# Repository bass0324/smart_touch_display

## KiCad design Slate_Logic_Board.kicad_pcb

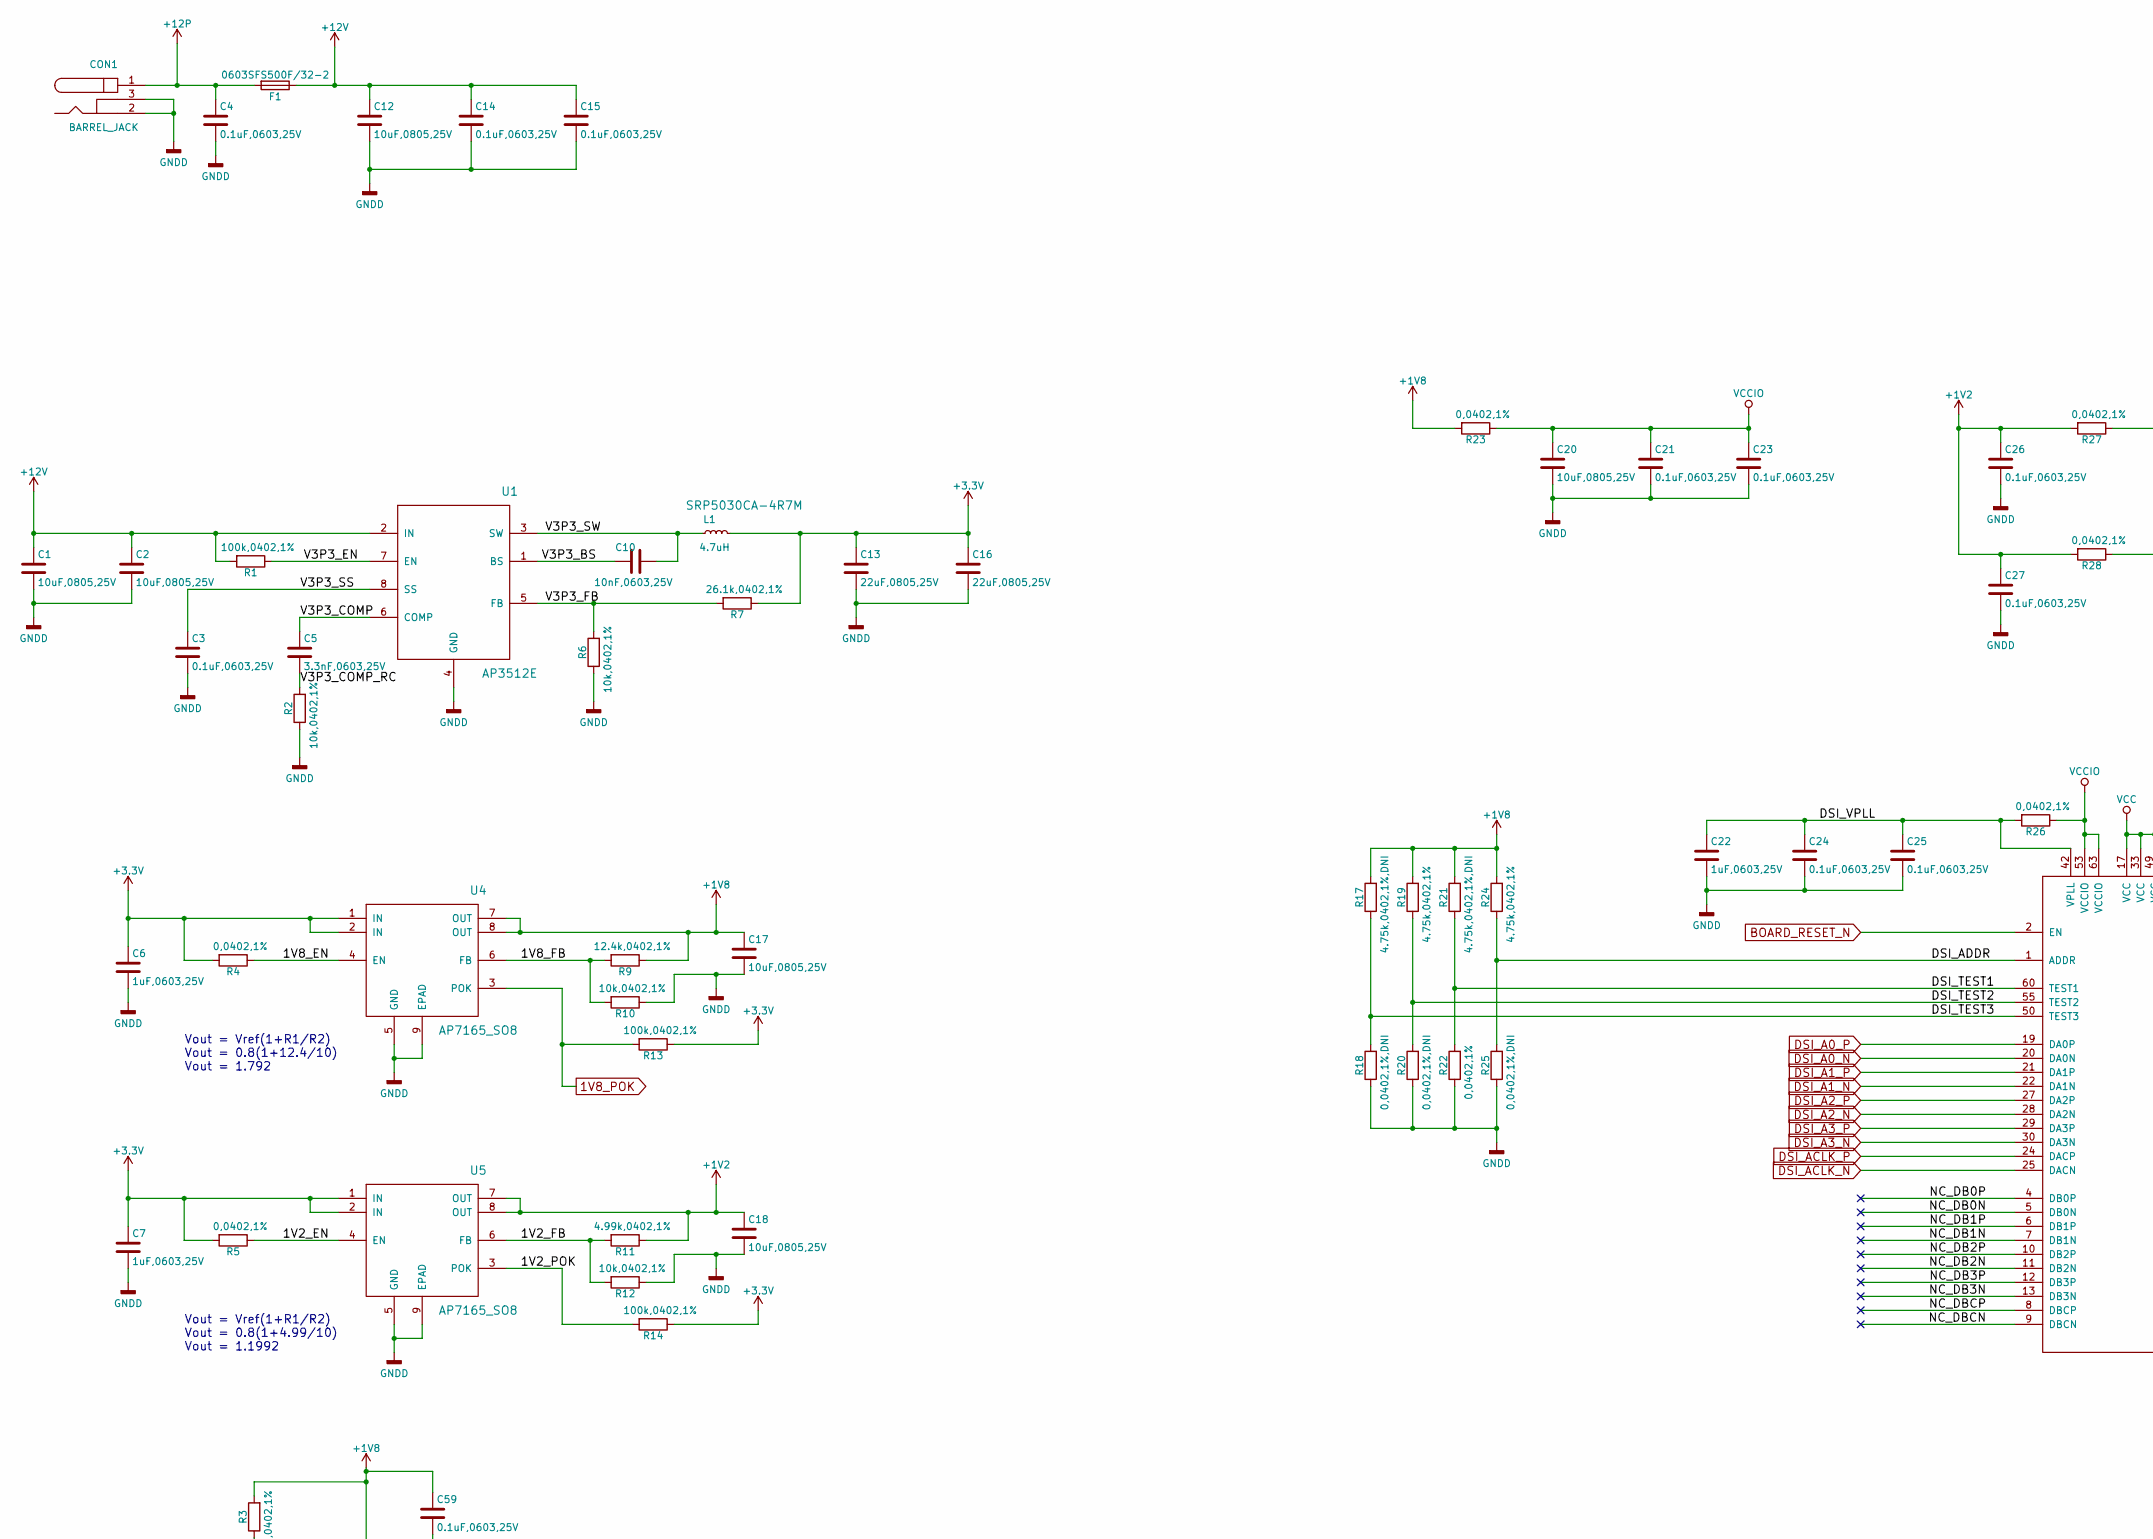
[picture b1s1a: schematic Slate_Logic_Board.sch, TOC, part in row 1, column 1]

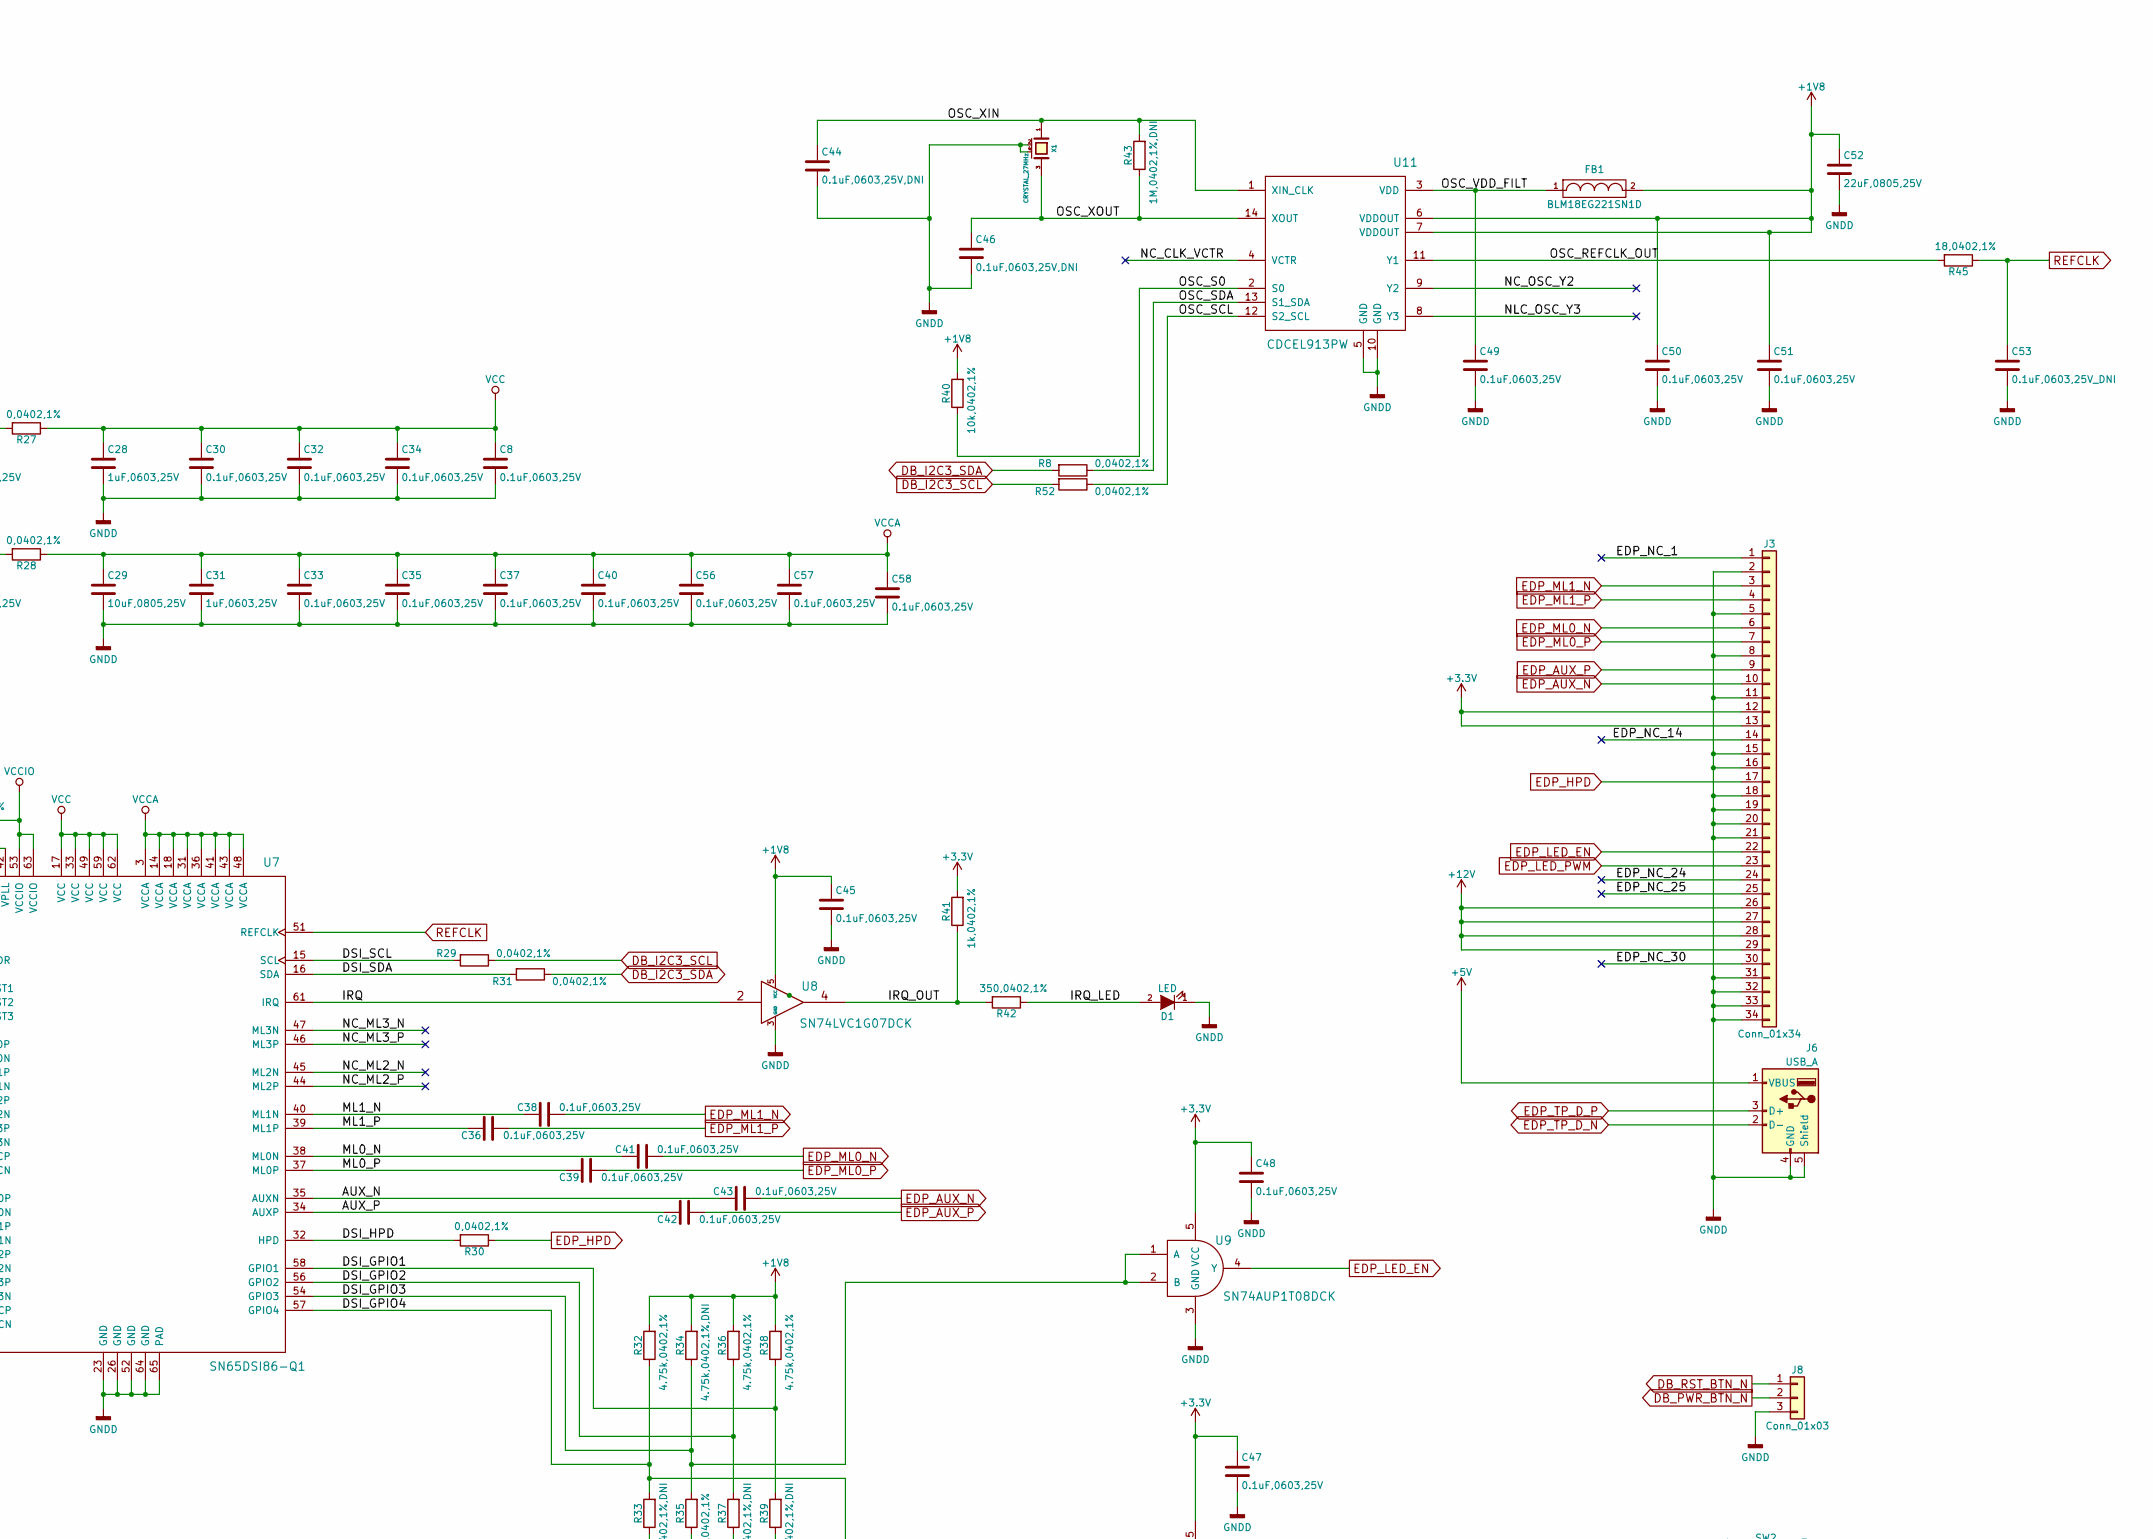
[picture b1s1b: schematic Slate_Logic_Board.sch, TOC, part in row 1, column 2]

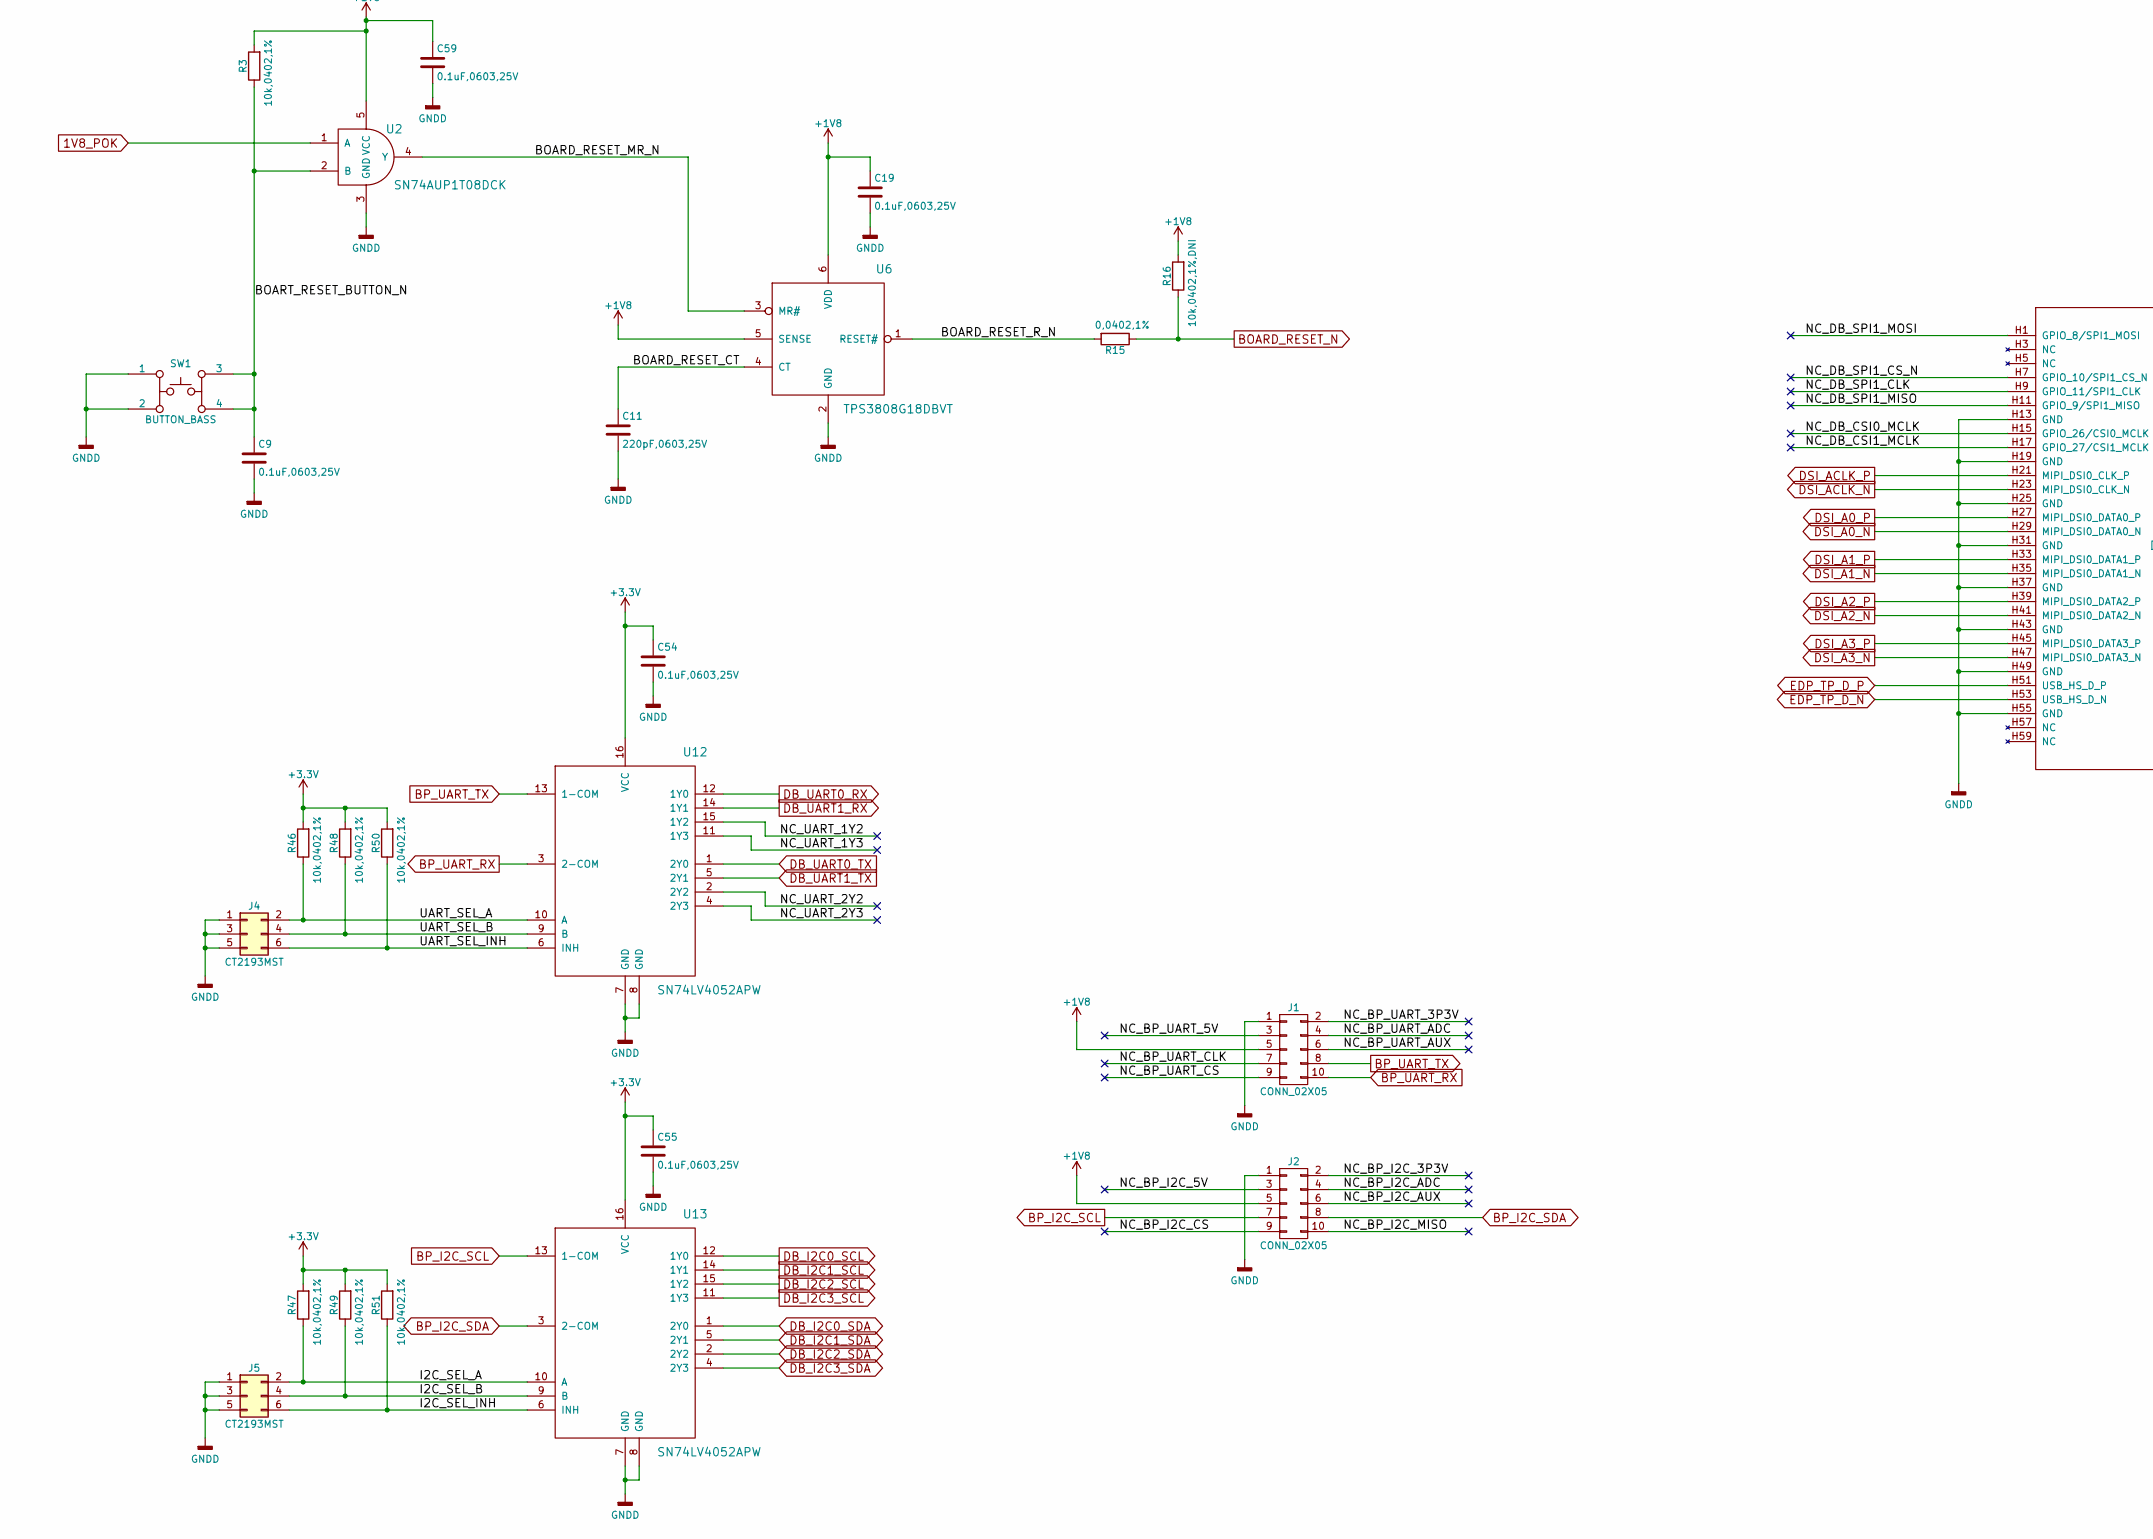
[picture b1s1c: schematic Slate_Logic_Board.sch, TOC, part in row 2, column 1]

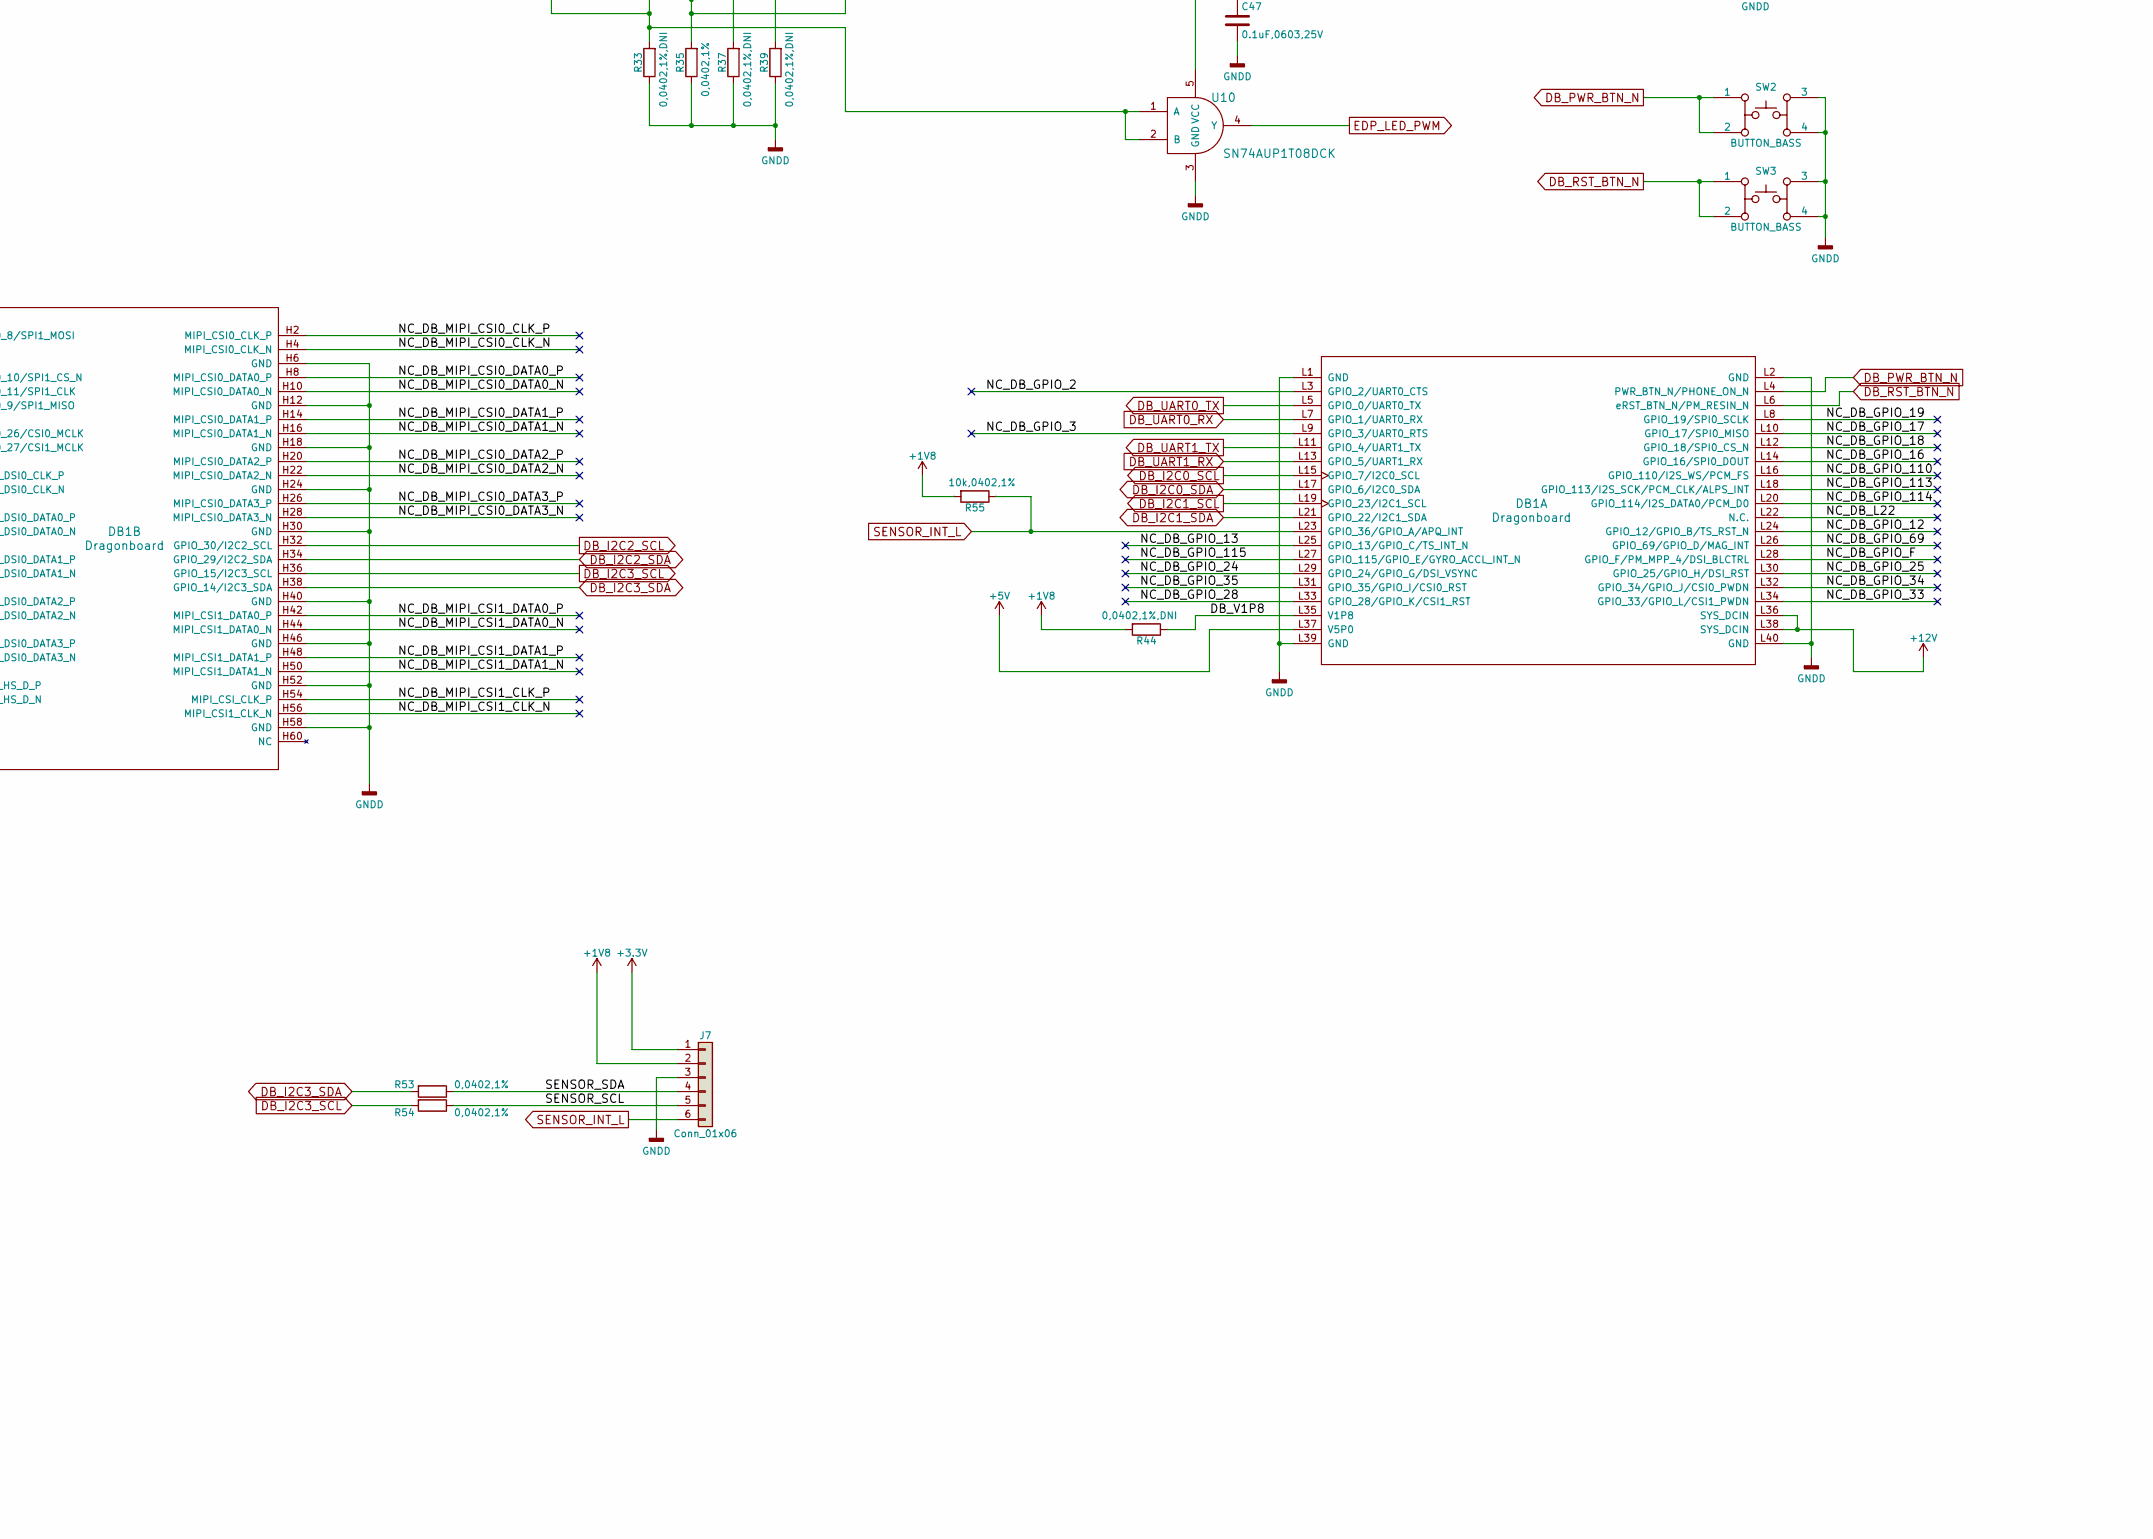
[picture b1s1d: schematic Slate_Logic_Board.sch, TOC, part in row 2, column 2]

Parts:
C1, C2, C12, C17, C18, C20, C29: 10uF,0805,25V; C_0805
C3, C4, C8, C9, C14, C15, C19, C21, C23, C24, C25, C26, C27, C30, C32, C33, C34, C35, C36, C37, C38, C39, C40, C41, C42, C43, C45, C47, C48, C49, C50, C51, C54, C55, C56, C57, C58, C59: 0.1uF,0603,25V; SMD_0603
C5: 3.3nF,0603,25V; SMD_0603
C6, C7, C22, C28, C31: 1uF,0603,25V; SMD_0603
C10: 10nF,0603,25V; SMD_0603
C11: 220pF,0603,25V; SMD_0603
C13, C16, C52: 22uF,0805,25V; C_0805
C44, C46: 0.1uF,0603,25V,DNI; SMD_0603
C53: 0.1uF,0603,25V_DNI; SMD_0603
CON1: BARREL_JACK
D1: LED; SMD_0603
DB1: Dragonboard; 96boards_baseboard
F1: 0603SFS500F/32-2; SMD_0603
FB1: BLM18EG221SN1D; SMD_0603
J1, J2: CONN_02X05; IDC-Header_2x05_Pitch2.54mm_Straight
J3: Conn_01x34; 20455-030E
J4, J5: CT2193MST
J6: USB_A
J7: Conn_01x06; Molex_PicoClasp_501331-0607_1x06_P1.0mm_Vertical
J8: Conn_01x03; Molex_PicoClasp_501331-0307_1x03_P1.0mm_Vertical
L1: 4.7uH; L_Bourns_SRP5030CA
R1, R13, R14: 100k,0402,1%; SMD_0603
R2, R3, R6, R10, R12, R40, R46, R47, R48, R49, R50, R51, R55: 10k,0402,1%; SMD_0603
R4, R5, R8, R15, R22, R23, R26, R27, R28, R29, R30, R31, R35, R52, R53, R54: 0,0402,1%; SMD_0603
R7: 26.1k,0402,1%; SMD_0603
R9: 12.4k,0402,1%; SMD_0603
R11: 4.99k,0402,1%; SMD_0603
R16: 10k,0402,1%,DNI; SMD_0603
R17, R21, R34: 4.75k,0402,1%,DNI; SMD_0603
R18, R20, R25, R33, R37, R39, R44: 0,0402,1%,DNI; SMD_0603
R19, R24, R32, R36, R38: 4.75k,0402,1%; SMD_0603
R41: 1k,0402,1%; SMD_0603
R42: 350,0402,1%; SMD_0603
R43: 1M,0402,1%,DNI; SMD_0603
R45: 18,0402,1%; SMD_0603
SW1, SW2, SW3: BUTTON_BASS; CK_PTS810
U1: AP3512E; SOIC-8-N
U2, U9, U10: SN74AUP1T08DCK; SOT23-5_65mm
U4, U5: AP7165_SO8; SOIC-8-N-AP7165
U6: TPS3808G18DBVT; SOT23-6_65mm
U7: SN65DSI86-Q1; HTQFP-64-1EP_10x10mm_Pitch0.5mm_ThermalPad_SN65DSIx6-Q1
U8: SN74LVC1G07DCK; SOT23-5_65mm
U11: CDCEL913PW; TSSOP-14_4.4x5mm_Pitch0.65mm
U12, U13: SN74LV4052APW; TSSOP16-0.65mm
X1: CRYSTAL_27MHz; 4pin-SMD-OSC

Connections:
1V8_POK: R13.2, U2.1 (A), U4.3 (POK)
+1V2: C18.1, C26.1, C27.1, R11.1, R27.2, R28.2, U5.7 (OUT), U5.8 (OUT)
+1V8: C17.1, C19.1, C45.1, C50.1, C51.1, C52.1, C59.1, FB1.2, J1.5, J2.5, J7.2, R3.2, R9.1, R16.2, R17.2, R19.2, R21.2, R23.2, R24.2, R32.2, R34.2, R36.2, R38.2, R40.2, R44.2, R55.2, U2.5 (VCC), U4.7 (OUT), U4.8 (OUT), U6.5 (SENSE), U6.6 (VDD), U8.5 (VCC), U11.6 (VDDOUT), U11.7 (VDDOUT)
+3V3: C6.1, C7.1, C13.1, C16.1, C47.1, C48.1, C54.1, C55.1, J3.12, J3.13, J7.1, L1.2, R4.2, R5.2, R7.1, R13.1, R14.1, R41.2, R46.2, R47.2, R48.2, R49.2, R50.2, R51.2, U4.1 (IN), U4.2 (IN), U5.1 (IN), U5.2 (IN), U9.5 (VCC), U10.5 (VCC), U12.16 (VCC), U13.16 (VCC)
+5V: DB1.L37 (V5P0), J6.1 (VBUS)
+12P: C4.1, CON1.1, F1.2
+12V: C1.1, C2.1, C12.1, C14.1, C15.1, DB1.L36 (SYS_DCIN), DB1.L38 (SYS_DCIN), F1.1, J3.26, J3.27, J3.28, J3.29, R1.2, U1.2 (IN)
/1V2_EN: R5.1, U5.4 (EN)
/1V2_FB: R11.2, R12.2, U5.6 (FB)
/1V2_POK: R14.2, U5.3 (POK)
/1V8_EN: R4.1, U4.4 (EN)
/1V8_FB: R9.2, R10.2, U4.6 (FB)
/AUX_N: C43.2, U7.35 (AUXN)
/AUX_P: C42.2, U7.34 (AUXP)
/BOARD_RESET_CT: C11.1, U6.4 (CT)
/BOARD_RESET_MR_N: U2.4 (Y), U6.3 (MR#)
/BOARD_RESET_R_N: R15.2, U6.1 (RESET#)
/BOART_RESET_BUTTON_N: C9.1, R3.1, SW1.3, SW1.4, U2.2 (B)
/DB_V1P8: DB1.L35 (V1P8), R44.1
/DSI_ADDR: R24.1, R25.2, U7.1 (ADDR)
/DSI_GPIO1: R38.1, R39.2, U7.58 (GPIO1)
/DSI_GPIO2: R36.1, R37.2, U7.56 (GPIO2)
/DSI_GPIO3: R34.1, R35.2, U7.54 (GPIO3), U9.1 (A), U9.2 (B)
/DSI_GPIO4: R32.1, R33.2, U7.57 (GPIO4), U10.1 (A), U10.2 (B)
/DSI_HPD: R30.2, U7.32 (HPD)
/DSI_SCL: R29.2, U7.15 (SCL)
/DSI_SDA: R31.2, U7.16 (SDA)
/DSI_TEST1: R21.1, R22.2, U7.60 (TEST1)
/DSI_TEST2: R19.1, R20.2, U7.55 (TEST2)
/DSI_TEST3: R17.1, R18.2, U7.50 (TEST3)
/DSI_VPLL: C22.1, C24.1, C25.1, R26.2, U7.42 (VPLL)
/EDP_NC_1: J3.1
/EDP_NC_14: J3.14
/EDP_NC_24: J3.24
/EDP_NC_25: J3.25
/EDP_NC_30: J3.30
/I2C_SEL_A: J5.2, R47.1, U13.10 (A)
/I2C_SEL_B: J5.4, R49.1, U13.9 (B)
/I2C_SEL_INH: J5.6, R51.1, U13.6 (INH)
/IRQ: U7.61 (IRQ), U8.2
/IRQ_LED: D1.2 (A), R42.1
/IRQ_OUT: R41.1, R42.2, U8.4
/ML0_N: C41.2, U7.38 (ML0N)
/ML0_P: C39.2, U7.37 (ML0P)
/ML1_N: C38.2, U7.40 (ML1N)
/ML1_P: C36.2, U7.39 (ML1P)
/NC_BP_I2C_3P3V: J2.2
/NC_BP_I2C_5V: J2.3
/NC_BP_I2C_ADC: J2.4
/NC_BP_I2C_AUX: J2.6
/NC_BP_I2C_CS: J2.9
/NC_BP_I2C_MISO: J2.10
/NC_BP_UART_3P3V: J1.2
/NC_BP_UART_5V: J1.3
/NC_BP_UART_ADC: J1.4
/NC_BP_UART_AUX: J1.6
/NC_BP_UART_CLK: J1.7
/NC_BP_UART_CS: J1.9
/NC_CLK_VCTR: U11.4 (VCTR)
/NC_DB0N: U7.5 (DB0N)
/NC_DB0P: U7.4 (DB0P)
/NC_DB1N: U7.7 (DB1N)
/NC_DB1P: U7.6 (DB1P)
/NC_DB2N: U7.11 (DB2N)
/NC_DB2P: U7.10 (DB2P)
/NC_DB3N: U7.13 (DB3N)
/NC_DB3P: U7.12 (DB3P)
/NC_DBCN: U7.9 (DBCN)
/NC_DBCP: U7.8 (DBCP)
/NC_DB_CSI0_MCLK: DB1.H15 (GPIO_26/CSI0_MCLK)
/NC_DB_CSI1_MCLK: DB1.H17 (GPIO_27/CSI1_MCLK)
/NC_DB_GPIO_2: DB1.L3 (GPIO_2/UART0_CTS)
/NC_DB_GPIO_3: DB1.L9 (GPIO_3/UART0_RTS)
/NC_DB_GPIO_12: DB1.L24 (GPIO_12/GPIO_B/TS_RST_N)
/NC_DB_GPIO_13: DB1.L25 (GPIO_13/GPIO_C/TS_INT_N)
/NC_DB_GPIO_16: DB1.L14 (GPIO_16/SPI0_DOUT)
/NC_DB_GPIO_17: DB1.L10 (GPIO_17/SPI0_MISO)
/NC_DB_GPIO_18: DB1.L12 (GPIO_18/SPI0_CS_N)
/NC_DB_GPIO_19: DB1.L8 (GPIO_19/SPI0_SCLK)
/NC_DB_GPIO_24: DB1.L29 (GPIO_24/GPIO_G/DSI_VSYNC)
/NC_DB_GPIO_25: DB1.L30 (GPIO_25/GPIO_H/DSI_RST)
/NC_DB_GPIO_28: DB1.L33 (GPIO_28/GPIO_K/CSI1_RST)
/NC_DB_GPIO_33: DB1.L34 (GPIO_33/GPIO_L/CSI1_PWDN)
/NC_DB_GPIO_34: DB1.L32 (GPIO_34/GPIO_J/CSI0_PWDN)
/NC_DB_GPIO_35: DB1.L31 (GPIO_35/GPIO_I/CSI0_RST)
/NC_DB_GPIO_69: DB1.L26 (GPIO_69/GPIO_D/MAG_INT)
/NC_DB_GPIO_110: DB1.L16 (GPIO_110/I2S_WS/PCM_FS)
/NC_DB_GPIO_113: DB1.L18 (GPIO_113/I2S_SCK/PCM_CLK/ALPS_INT)
/NC_DB_GPIO_114: DB1.L20 (GPIO_114/I2S_DATA0/PCM_D0)
/NC_DB_GPIO_115: DB1.L27 (GPIO_115/GPIO_E/GYRO_ACCL_INT_N)
/NC_DB_GPIO_F: DB1.L28 (GPIO_F/PM_MPP_4/DSI_BLCTRL)
/NC_DB_L22: DB1.L22 (N.C.)
/NC_DB_MIPI_CSI0_CLK_N: DB1.H4 (MIPI_CSI0_CLK_N)
/NC_DB_MIPI_CSI0_CLK_P: DB1.H2 (MIPI_CSI0_CLK_P)
/NC_DB_MIPI_CSI0_DATA0_N: DB1.H10 (MIPI_CSI0_DATA0_N)
/NC_DB_MIPI_CSI0_DATA0_P: DB1.H8 (MIPI_CSI0_DATA0_P)
/NC_DB_MIPI_CSI0_DATA1_N: DB1.H16 (MIPI_CSI0_DATA1_N)
/NC_DB_MIPI_CSI0_DATA1_P: DB1.H14 (MIPI_CSI0_DATA1_P)
/NC_DB_MIPI_CSI0_DATA2_N: DB1.H22 (MIPI_CSI0_DATA2_N)
/NC_DB_MIPI_CSI0_DATA2_P: DB1.H20 (MIPI_CSI0_DATA2_P)
/NC_DB_MIPI_CSI0_DATA3_N: DB1.H28 (MIPI_CSI0_DATA3_N)
/NC_DB_MIPI_CSI0_DATA3_P: DB1.H26 (MIPI_CSI0_DATA3_P)
/NC_DB_MIPI_CSI1_CLK_N: DB1.H56 (MIPI_CSI1_CLK_N)
/NC_DB_MIPI_CSI1_CLK_P: DB1.H54 (MIPI_CSI_CLK_P)
/NC_DB_MIPI_CSI1_DATA0_N: DB1.H44 (MIPI_CSI1_DATA0_N)
/NC_DB_MIPI_CSI1_DATA0_P: DB1.H42 (MIPI_CSI1_DATA0_P)
/NC_DB_MIPI_CSI1_DATA1_N: DB1.H50 (MIPI_CSI1_DATA1_N)
/NC_DB_MIPI_CSI1_DATA1_P: DB1.H48 (MIPI_CSI1_DATA1_P)
/NC_DB_SPI1_CLK: DB1.H9 (GPIO_11/SPI1_CLK)
/NC_DB_SPI1_CS_N: DB1.H7 (GPIO_10/SPI1_CS_N)
/NC_DB_SPI1_MISO: DB1.H11 (GPIO_9/SPI1_MISO)
/NC_DB_SPI1_MOSI: DB1.H1 (GPIO_8/SPI1_MOSI)
/NC_ML2_N: U7.45 (ML2N)
/NC_ML2_P: U7.44 (ML2P)
/NC_ML3_N: U7.47 (ML3N)
/NC_ML3_P: U7.46 (ML3P)
/NC_OSC_Y2: U11.9 (Y2)
/NC_UART_1Y2: U12.15 (1Y2)
/NC_UART_1Y3: U12.11 (1Y3)
/NC_UART_2Y2: U12.2 (2Y2)
/NC_UART_2Y3: U12.4 (2Y3)
/NLC_OSC_Y3: U11.8 (Y3)
/OSC_REFCLK_OUT: R45.2, U11.11 (Y1)
/OSC_S0: R40.1, U11.2 (S0)
/OSC_SCL: R52.1, U11.12 (S2_SCL)
/OSC_SDA: R8.1, U11.13 (S1_SDA)
/OSC_VDD_FILT: C49.1, FB1.1, U11.3 (VDD)
/OSC_XIN: C44.1, R43.2, U11.1 (XIN_CLK), X1.1
/OSC_XOUT: C46.1, R43.1, U11.14 (XOUT), X1.3
/SENSOR_SCL: J7.5, R54.1
/SENSOR_SDA: J7.4, R53.1
/UART_SEL_A: J4.2, R46.1, U12.10 (A)
/UART_SEL_B: J4.4, R48.1, U12.9 (B)
/UART_SEL_INH: J4.6, R50.1, U12.6 (INH)
/V3P3_BS: C10.2, U1.1 (BS)
/V3P3_COMP: C5.1, U1.6 (COMP)
/V3P3_COMP_RC: C5.2, R2.2
/V3P3_EN: R1.1, U1.7 (EN)
/V3P3_FB: R6.2, R7.2, U1.5 (FB)
/V3P3_SS: C3.1, U1.8 (SS)
/V3P3_SW: C10.1, L1.1, U1.3 (SW)
BOARD_RESET_N: R15.1, R16.1, U7.2 (EN)
BP_I2C_SCL: J2.7, U13.13 (1-COM)
BP_I2C_SDA: J2.8, U13.3 (2-COM)
BP_UART_RX: J1.10, U12.3 (2-COM)
BP_UART_TX: J1.8, U12.13 (1-COM)
DB_I2C0_SCL: DB1.L15 (GPIO_7/I2C0_SCL), U13.12 (1Y0)
DB_I2C0_SDA: DB1.L17 (GPIO_6/I2C0_SDA), U13.1 (2Y0)
DB_I2C1_SCL: DB1.L19 (GPIO_23/I2C1_SCL), U13.14 (1Y1)
DB_I2C1_SDA: DB1.L21 (GPIO_22/I2C1_SDA), U13.5 (2Y1)
DB_I2C2_SCL: DB1.H32 (GPIO_30/I2C2_SCL), U13.15 (1Y2)
DB_I2C2_SDA: DB1.H34 (GPIO_29/I2C2_SDA), U13.2 (2Y2)
DB_I2C3_SCL: DB1.H36 (GPIO_15/I2C3_SCL), R29.1, R52.2, R54.2, U13.11 (1Y3)
DB_I2C3_SDA: DB1.H38 (GPIO_14/I2C3_SDA), R8.2, R31.1, R53.2, U13.4 (2Y3)
DB_PWR_BTN_N: DB1.L4 (PWR_BTN_N/PHONE_ON_N), J8.2, SW2.1, SW2.2
DB_RST_BTN_N: DB1.L6 (eRST_BTN_N/PM_RESIN_N), J8.1, SW3.1, SW3.2
DB_UART0_RX: DB1.L7 (GPIO_1/UART0_RX), U12.12 (1Y0)
DB_UART0_TX: DB1.L5 (GPIO_0/UART0_TX), U12.1 (2Y0)
DB_UART1_RX: DB1.L13 (GPIO_5/UART1_RX), U12.14 (1Y1)
DB_UART1_TX: DB1.L11 (GPIO_4/UART1_TX), U12.5 (2Y1)
DSI_A0_N: DB1.H29 (MIPI_DSI0_DATA0_N), U7.20 (DA0N)
DSI_A0_P: DB1.H27 (MIPI_DSI0_DATA0_P), U7.19 (DA0P)
DSI_A1_N: DB1.H35 (MIPI_DSI0_DATA1_N), U7.22 (DA1N)
DSI_A1_P: DB1.H33 (MIPI_DSI0_DATA1_P), U7.21 (DA1P)
DSI_A2_N: DB1.H41 (MIPI_DSI0_DATA2_N), U7.28 (DA2N)
DSI_A2_P: DB1.H39 (MIPI_DSI0_DATA2_P), U7.27 (DA2P)
DSI_A3_N: DB1.H47 (MIPI_DSI0_DATA3_N), U7.30 (DA3N)
DSI_A3_P: DB1.H45 (MIPI_DSI0_DATA3_P), U7.29 (DA3P)
DSI_ACLK_N: DB1.H23 (MIPI_DSI0_CLK_N), U7.25 (DACN)
DSI_ACLK_P: DB1.H21 (MIPI_DSI0_CLK_P), U7.24 (DACP)
EDP_AUX_N: C43.1, J3.10
EDP_AUX_P: C42.1, J3.9
EDP_HPD: J3.17, R30.1
EDP_LED_EN: J3.22, U9.4 (Y)
EDP_LED_PWM: J3.23, U10.4 (Y)
EDP_ML0_N: C41.1, J3.6
EDP_ML0_P: C39.1, J3.7
EDP_ML1_N: C38.1, J3.3
EDP_ML1_P: C36.1, J3.4
EDP_TP_D_N: DB1.H53 (USB_HS_D_N), J6.2 (D-)
EDP_TP_D_P: DB1.H51 (USB_HS_D_P), J6.3 (D+)
GNDD: C1.2, C2.2, C3.2, C4.2, C6.2, C7.2, C8.2, C9.2, C11.2, C12.2, C13.2, C14.2, C15.2, C16.2, C17.2, C18.2, C19.2, C20.2, C21.2, C22.2, C23.2, C24.2, C25.2, C26.2, C27.2, C28.2, C29.2, C30.2, C31.2, C32.2, C33.2, C34.2, C35.2, C37.2, C40.2, C44.2, C45.2, C46.2, C47.2, C48.2, C49.2, C50.2, C51.2, C52.2, C53.2, C54.2, C55.2, C56.2, C57.2, C58.2, C59.2, CON1.2, CON1.3, D1.1 (K), DB1.H6 (GND), DB1.H12 (GND), DB1.H13 (GND), DB1.H18 (GND), DB1.H19 (GND), DB1.H24 (GND), DB1.H25 (GND), DB1.H30 (GND), DB1.H31 (GND), DB1.H37 (GND), DB1.H40 (GND), DB1.H43 (GND), DB1.H46 (GND), DB1.H49 (GND), DB1.H52 (GND), DB1.H55 (GND), DB1.H58 (GND), DB1.L1 (GND), DB1.L2 (GND), DB1.L39 (GND), DB1.L40 (GND), J1.1, J2.1, J3.2, J3.5, J3.8, J3.11, J3.15, J3.16, J3.18, J3.19, J3.20, J3.21, J3.31, J3.32, J3.33, J3.34, J4.1, J4.3, J4.5, J5.1, J5.3, J5.5, J6.4 (GND), J6.5 (Shield), J7.3, J8.3, R2.1, R6.1, R10.1, R12.1, R18.1, R20.1, R22.1, R25.1, R33.1, R35.1, R37.1, R39.1, SW1.1, SW1.2, SW2.3, SW2.4, SW3.3, SW3.4, U1.4 (GND), U2.3 (GND), U4.5 (GND), U4.9 (EPAD), U5.5 (GND), U5.9 (EPAD), U6.2 (GND), U7.23 (GND), U7.26 (GND), U7.52 (GND), U7.64 (GND), U7.65 (PAD), U8.3 (GND), U9.3 (GND), U10.3 (GND), U11.5 (GND), U11.10 (GND), U12.7 (GND), U12.8 (GND), U13.7 (GND), U13.8 (GND), X1.2 (case), X1.4
REFCLK: C53.1, R45.1, U7.51 (REFCLK)
SENSOR_INT_L: DB1.L23 (GPIO_36/GPIO_A/APQ_INT), J7.6, R55.1
VCC: C8.1, C28.1, C30.1, C32.1, C34.1, R27.1, U7.17 (VCC), U7.33 (VCC), U7.49 (VCC), U7.59 (VCC), U7.62 (VCC)
VCCA: C29.1, C31.1, C33.1, C35.1, C37.1, C40.1, C56.1, C57.1, C58.1, R28.1, U7.3 (VCCA), U7.14 (VCCA), U7.18 (VCCA), U7.31 (VCCA), U7.36 (VCCA), U7.41 (VCCA), U7.43 (VCCA), U7.48 (VCCA)
VCCIO: C20.1, C21.1, C23.1, R23.1, R26.1, U7.53 (VCCIO), U7.63 (VCCIO)

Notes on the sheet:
Vout = Vref(1+R1/R2) Vout = 0.8(1+12.4/10) Vout = 1.792
Vout = Vref(1+R1/R2) Vout = 0.8(1+4.99/10) Vout = 1.1992

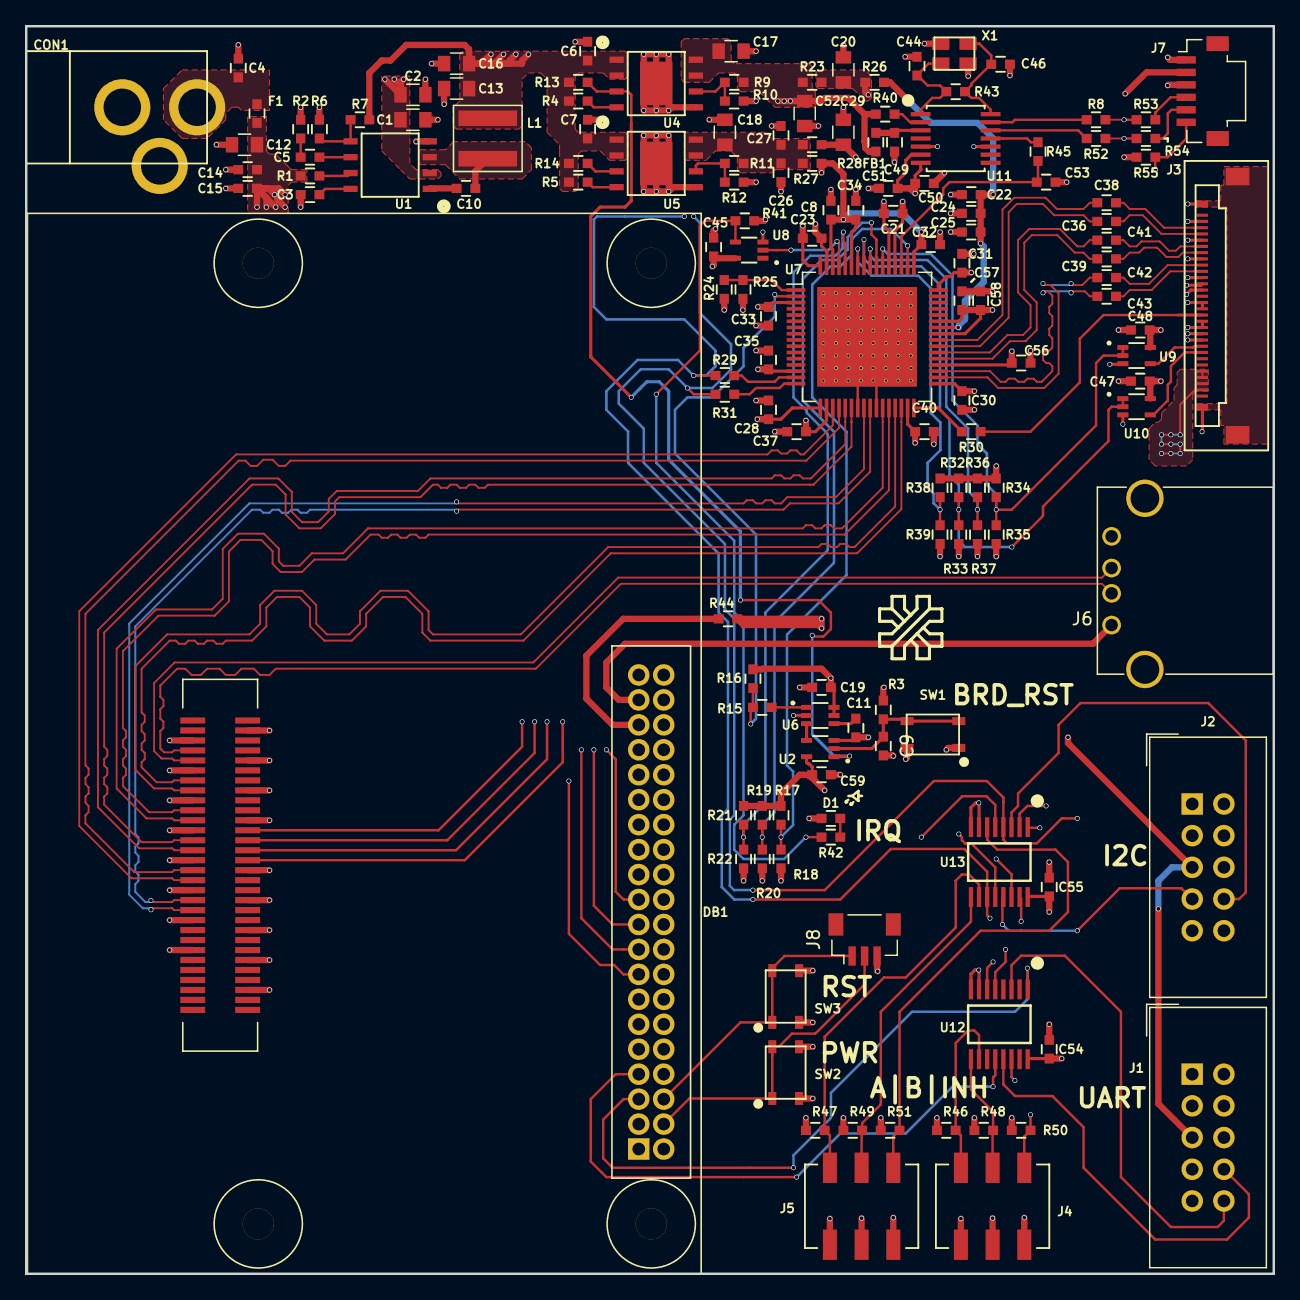
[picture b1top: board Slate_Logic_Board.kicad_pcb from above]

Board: 4 copper layers, 100.0 x 100.0 mm, 144 parts (1 on the bottom side), 106 nets.

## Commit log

2019-06-22 Initial Upload
    Prototype files uploaded to github
